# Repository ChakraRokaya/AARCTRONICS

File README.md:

# AARCTRONICS
 AARCTRONICS- All kinds of the schematic design and PCB design, hardware implementation and functional testing.

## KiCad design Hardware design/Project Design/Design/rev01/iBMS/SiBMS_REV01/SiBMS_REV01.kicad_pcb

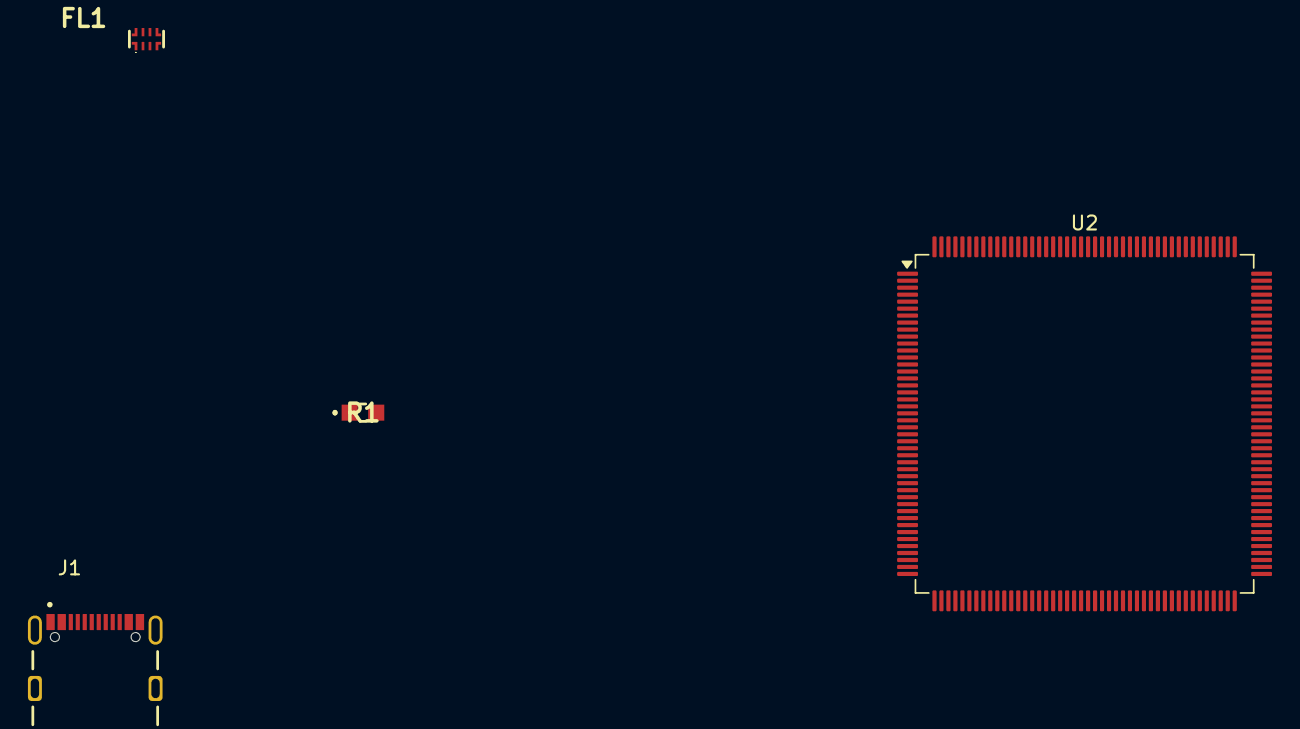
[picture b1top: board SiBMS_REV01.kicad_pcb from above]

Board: 2 copper layers, 4 parts (0 on the bottom side), 2 nets, no tracks yet.

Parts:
FL1: ECMF02-4CMX8; ECMF024CMX8
J1: USB4105GFA060
R1: ERA-6AED512V; ERA6AEB1020V
U2: STM32H747IGTx; LQFP-176_24x24mm_P0.5mm

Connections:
unnamed: U2.6 (VSS), U2.12 (VSS), U2.24 (VSS), U2.45 (VSS), U2.47 (VSS), U2.64 (VSS), U2.70 (VSS), U2.81 (VSS), U2.83 (VSS), U2.93 (VSS), U2.100 (VSS), U2.112 (VSS), U2.119 (VSS), U2.134 (VSS), U2.137 (VSS), U2.151 (VSS), U2.159 (VSS), U2.173 (VSS)
unnamed: U2.105 (VSSDSI), U2.109 (VSSDSI)

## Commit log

2024-07-25 Initation
    @AARCTRONICS
    @Folder structure and commit
    @ Product design and Resources- Templates
2024-07-26 Updated and arranging folders
    @Rearrange the folder structure
    @Added a embedded C code for UART protocol
2024-07-26 Create Read Me
2024-08-04 arduino coding
    added arduino cell series coding examples
2024-11-26 @deleted unnecessary files
    deleted some files
